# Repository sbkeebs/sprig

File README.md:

★ 10 columns in a modified Katana layout

★ inner columns are moved down a bit for an ergo-light curve

★ spacebar layout supports ISO enter for either or both bars

### This repo should contain:
- KiCAD 8 files for the PCB
- production files (gerbers, JLC BOM, CPL, etc) -- definitely double check the part numbers/availability before committing to fabrication! 
- printable files for the case (i am not very experienced in 3D design, but i have confirmed that it works!)
- firmware in both qmk/vial and zmk, and source for each

### To build your own zmk keymap
Fork [this repo](https://github.com/sbkeebs/sprig-zmk-config), and enable Actions. Modify `config/boards/arm/sprig/sprig.keymap`. Let it build (click Actions at the top of your repo).

ZMK Studio is not yet integrated!

This was built upon NCKiser's [STM32F072 template](https://github.com/NCKiser/STM32F072_template) as one of my first projects with an integrated MCU. If you'd like to get started with your own keyboard, [this video](https://www.youtube.com/watch?v=kGKN8SGkUD0) is a great place to start.

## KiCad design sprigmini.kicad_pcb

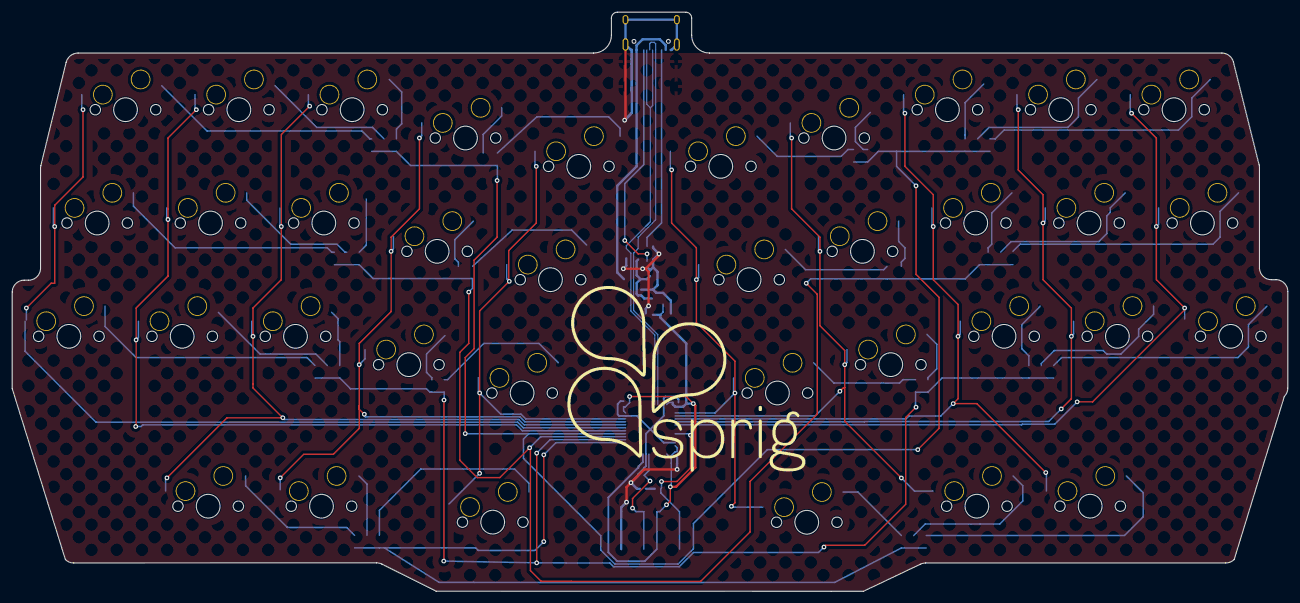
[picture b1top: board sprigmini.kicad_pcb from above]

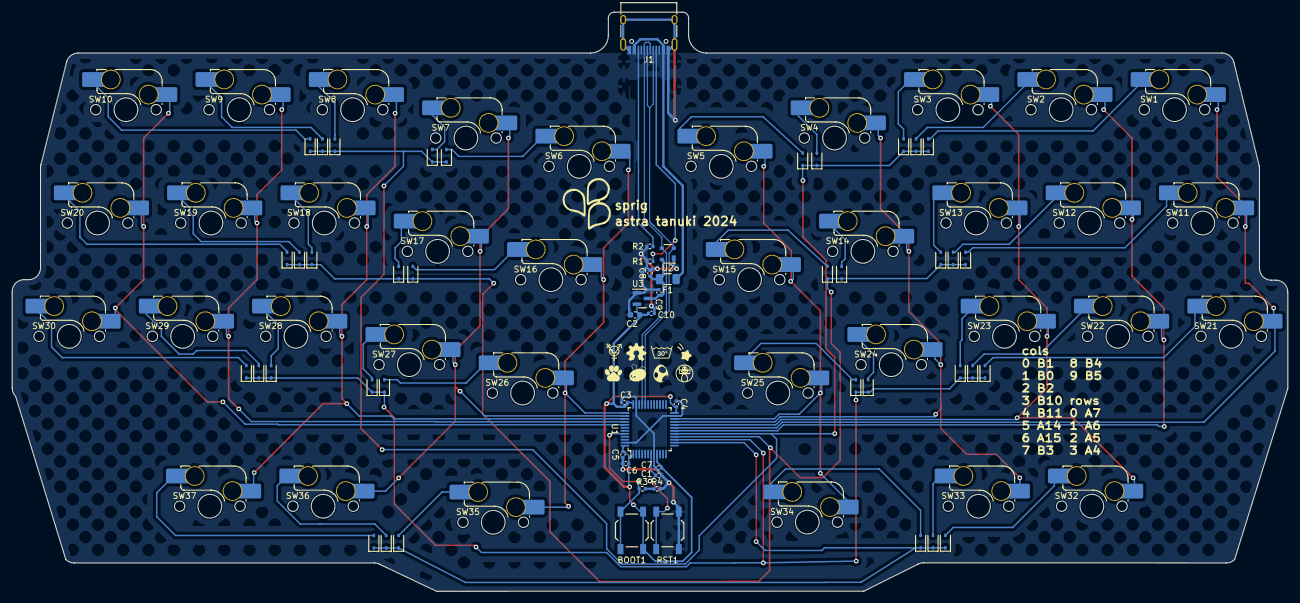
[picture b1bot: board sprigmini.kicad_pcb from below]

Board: 2 copper layers, 214.4 x 97.4 mm, 93 parts (93 on the bottom side), 61 nets.

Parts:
BOOT1: SW_SPST; SW_SPST_TL3342
C1, C3, C4, C5, C6, C7, C8: 100nF; C_0402_1005Metric
C2: 10uF; C_0603_1608Metric
C9, C10: 1uF; C_0402_1005Metric
D1, D2, D3, D4, D5, D6, D7, D8, D9, D10, D11, D12, D13, D14, D15, D16, D17, D18, D19, D20, D21, D22, D23, D24, D25, D26, D27, D28, D29, D30, D32, D33, D34, D35, D36, D37: D_Small; D_SOD-323
F1: 500mA; Fuse_1206_3216Metric
J1: USB_C_Receptacle_USB2.0; USB_C_Receptacle_HRO_TYPE-C-31-M-12
R1, R2, R3, R4: 5.1k; R_0402_1005Metric
RST1: SW_SPST; SW_SPST_TL3342
SW1, SW2, SW3, SW4, SW5, SW6, SW7, SW8, SW9, SW10, SW11, SW12, SW13, SW14, SW15, SW16, SW17, SW18, SW19, SW20, SW21, SW22, SW23, SW24, SW25, SW26, SW27, SW28, SW29, SW30, SW32, SW33, SW34, SW35, SW36, SW37: MX_SW_HS; SW_MX_HS_CPG151101S11_1u
U1: STM32F072CBT6; LQFP-48_7x7mm_P0.5mm
U2: PRTR5V0U2X; SOT-143
U3: XC6206PxxxMR-Regulator_Linear; SOT-23

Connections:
+3V3: BOOT1.1 (A), C2.1, C3.1, C4.1, C5.1, C6.1, C7.1, C10.1, U1.1 (VBAT), U1.9 (VDDA), U1.24 (VDD), U1.36 (VDDIO2), U1.48 (VDD), U3.2 (VO)
+5V: C8.1, C9.1, F1.2, U2.4 (VCC), U3.3 (VI)
BOOT0: BOOT1.2 (B), R3.1, U1.44 (BOOT0)
D+: J1.A6 (D+), J1.B6 (D+), U1.33 (PA12), U2.3 (I/O2)
D-: J1.A7 (D-), J1.B7 (D-), U1.32 (PA11), U2.2 (I/O1)
GND: C1.2, C2.2, C3.2, C4.2, C5.2, C6.2, C7.2, C8.2, C9.2, C10.2, J1.A1 (GND), J1.A12 (GND), J1.B1 (GND), J1.B12 (GND), J1.S1 (SHIELD), R1.1, R2.2, R4.2, RST1.2 (B), U1.8 (VSSA), U1.23 (VSS), U1.35 (VSS), U1.47 (VSS), U2.1 (GND), U3.1 (GND)
NRST: C1.1, RST1.1 (A), U1.7 (NRST)
unnamed: D1.2 (A), SW1.2
unnamed: D2.2 (A), SW2.2
unnamed: D3.2 (A), SW3.2
unnamed: D4.2 (A), SW4.2
unnamed: D5.2 (A), SW5.2
unnamed: D6.2 (A), SW6.2
unnamed: D7.2 (A), SW7.2
unnamed: D8.2 (A), SW8.2
unnamed: D9.2 (A), SW9.2
unnamed: D10.2 (A), SW10.2
unnamed: D11.2 (A), SW11.2
unnamed: D12.2 (A), SW12.2
unnamed: D13.2 (A), SW13.2
unnamed: D14.2 (A), SW14.2
unnamed: D15.2 (A), SW15.2
unnamed: D16.2 (A), SW16.2
unnamed: D17.2 (A), SW17.2
unnamed: D18.2 (A), SW18.2
unnamed: D19.2 (A), SW19.2
unnamed: D20.2 (A), SW20.2
unnamed: D21.2 (A), SW21.2
unnamed: D22.2 (A), SW22.2
unnamed: D23.2 (A), SW23.2
unnamed: D24.2 (A), SW24.2
unnamed: D25.2 (A), SW25.2
unnamed: D26.2 (A), SW26.2
unnamed: D27.2 (A), SW27.2
unnamed: D28.2 (A), SW28.2
unnamed: D29.2 (A), SW29.2
unnamed: D30.2 (A), SW30.2
unnamed: D32.2 (A), SW32.2
unnamed: D33.2 (A), SW33.2
unnamed: D34.2 (A), SW34.2
unnamed: D35.2 (A), SW35.2
unnamed: D36.2 (A), SW36.2
unnamed: D37.2 (A), SW37.2
unnamed: J1.A5 (CC1), R1.2
unnamed: J1.B5 (CC2), R2.1
unnamed: R3.2, R4.1
VBUS: F1.1, J1.A4 (VBUS), J1.A9 (VBUS), J1.B4 (VBUS), J1.B9 (VBUS)
col 0: SW1.1, SW11.1, SW21.1, U1.19 (PB1)
col 1: SW2.1, SW12.1, SW22.1, U1.18 (PB0)
col 2: SW3.1, SW13.1, SW23.1, SW32.1, U1.20 (PB2)
col 3: SW4.1, SW14.1, SW24.1, SW33.1, U1.21 (PB10)
col 4: SW5.1, SW15.1, SW25.1, SW34.1, U1.22 (PB11)
col 5: SW6.1, SW16.1, SW26.1, SW35.1, U1.37 (PA14)
col 6: SW7.1, SW17.1, SW27.1, SW36.1, U1.38 (PA15)
col 7: SW8.1, SW18.1, SW28.1, SW37.1, U1.39 (PB3)
col 8: SW9.1, SW19.1, SW29.1, U1.40 (PB4)
col 9: SW10.1, SW20.1, SW30.1, U1.41 (PB5)
row 0: D1.1 (K), D2.1 (K), D3.1 (K), D4.1 (K), D5.1 (K), D6.1 (K), D7.1 (K), D8.1 (K), D9.1 (K), D10.1 (K), U1.17 (PA7)
row 1: D11.1 (K), D12.1 (K), D13.1 (K), D14.1 (K), D15.1 (K), D16.1 (K), D17.1 (K), D18.1 (K), D19.1 (K), D20.1 (K), U1.16 (PA6)
row 2: D21.1 (K), D22.1 (K), D23.1 (K), D24.1 (K), D25.1 (K), D26.1 (K), D27.1 (K), D28.1 (K), D29.1 (K), D30.1 (K), U1.15 (PA5)
row 3: D32.1 (K), D33.1 (K), D34.1 (K), D35.1 (K), D36.1 (K), D37.1 (K), U1.14 (PA4)

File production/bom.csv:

Designator,Footprint,Quantity,Value,LCSC Part #
"BOOT1, RST1",SW_SPST_TL3342,2,SW_SPST,C318884
"C1, C3, C4, C5, C6, C7, C8",0402,7,100nF,C1525
"C10, C9",0402,2,1uF,C52923
C2,0603,1,10uF,C57112
"D1, D10, D11, D12, D13, D14, D15, D16, D17, D18, D19, D2, D20, D21, D22, D23, D24, D25, D26, D27, D28, D29, D3, D30, D32, D33, D34, D35, D36, D37, D4, D5, D6, D7, D8, D9",D_SOD-323,36,D_Small,C908234
F1,1206,1,500mA,C70076
J1,USB_C_Receptacle_HRO_TYPE-C-31-M-12,1,USB_C_Receptacle_USB2.0,C165948
"R1, R2, R3, R4",0402,4,5.1k,C144745
U1,LQFP-48_7x7mm_P0.5mm,1,STM32F072CBT6,C81720
U2,SOT-143,1,PRTR5V0U2X,C2827688
U3,SOT-23,1,XC6206PxxxMR-Regulator_Linear,C5446

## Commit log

2024-07-26 first version
2024-07-26 fix vial fw
2024-07-26 remove zmk
2024-07-26 readd zmk
2024-07-26 add logo svg
2024-07-26 add logo
2024-07-26 add flashable zmk file
2024-07-27 reorganize
2024-07-27 add photo
2024-07-27 replace old case file, include .step also
2024-07-27 update pcb files
